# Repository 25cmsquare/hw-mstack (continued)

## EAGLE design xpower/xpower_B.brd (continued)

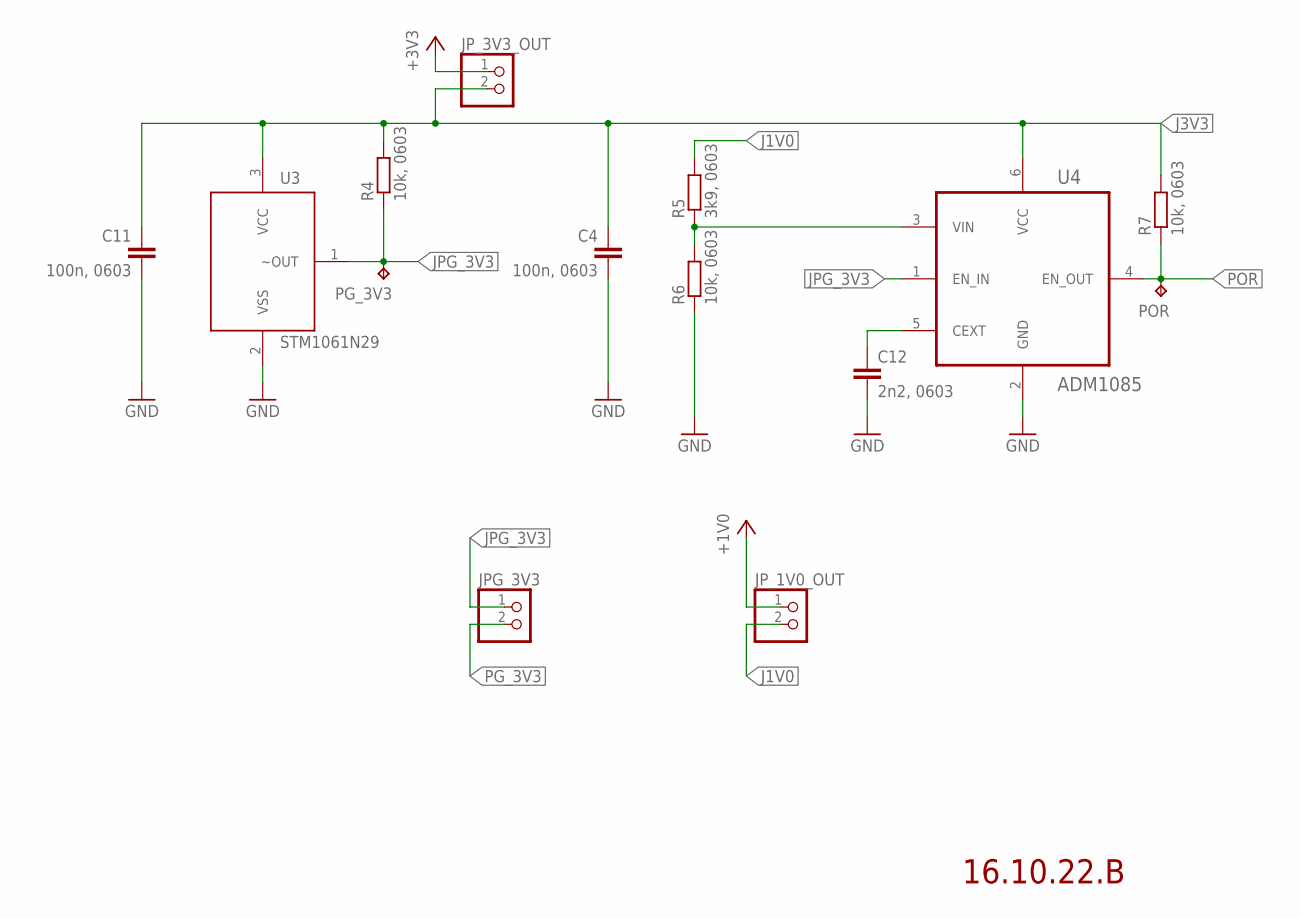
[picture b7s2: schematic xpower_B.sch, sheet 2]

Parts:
C4, C11: 100n, 0603; C0603
C12: 2n2, 0603; C0603
JPG_3V3: PINHD-1X2; 1X02
JP_1V0_OUT, JP_3V3_OUT: PINHD-1X2; 1X02
PG_3V3: TPTP14R; TP14R
POR: TPTP14R; TP14R
R4, R6, R7: 10k, 0603; R0603
R5: 3k9, 0603; R0603
U3: STM1061N29; SOT-23-3
U4: ADM1085; SOT65P210X110-6N

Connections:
+1V0: JP_1V0_OUT.1; also elsewhere on the board
+3V3: JP_3V3_OUT.1; also elsewhere on the board
CEXT: C12.1, U4.5 (CEXT)
GND: C4.2, C11.2, C12.2, R6.1, U3.2 (VSS), U4.2 (GND); also elsewhere on the board
J1V0: JP_1V0_OUT.2, R5.2
J3V3: C4.1, C11.1, JP_3V3_OUT.2, R4.2, R7.2, U3.3 (VCC), U4.6 (VCC)
JPG_3V3: JPG_3V3.1, PG_3V3.TP, R4.1, U3.1 (~OUT), U4.1 (EN_IN)
PG_3V3: JPG_3V3.2; also elsewhere on the board
POR: POR.TP, R7.1, U4.4 (EN_OUT); also elsewhere on the board
VIN: R5.1, R6.2, U4.3 (VIN)

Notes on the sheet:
16.10.22.B

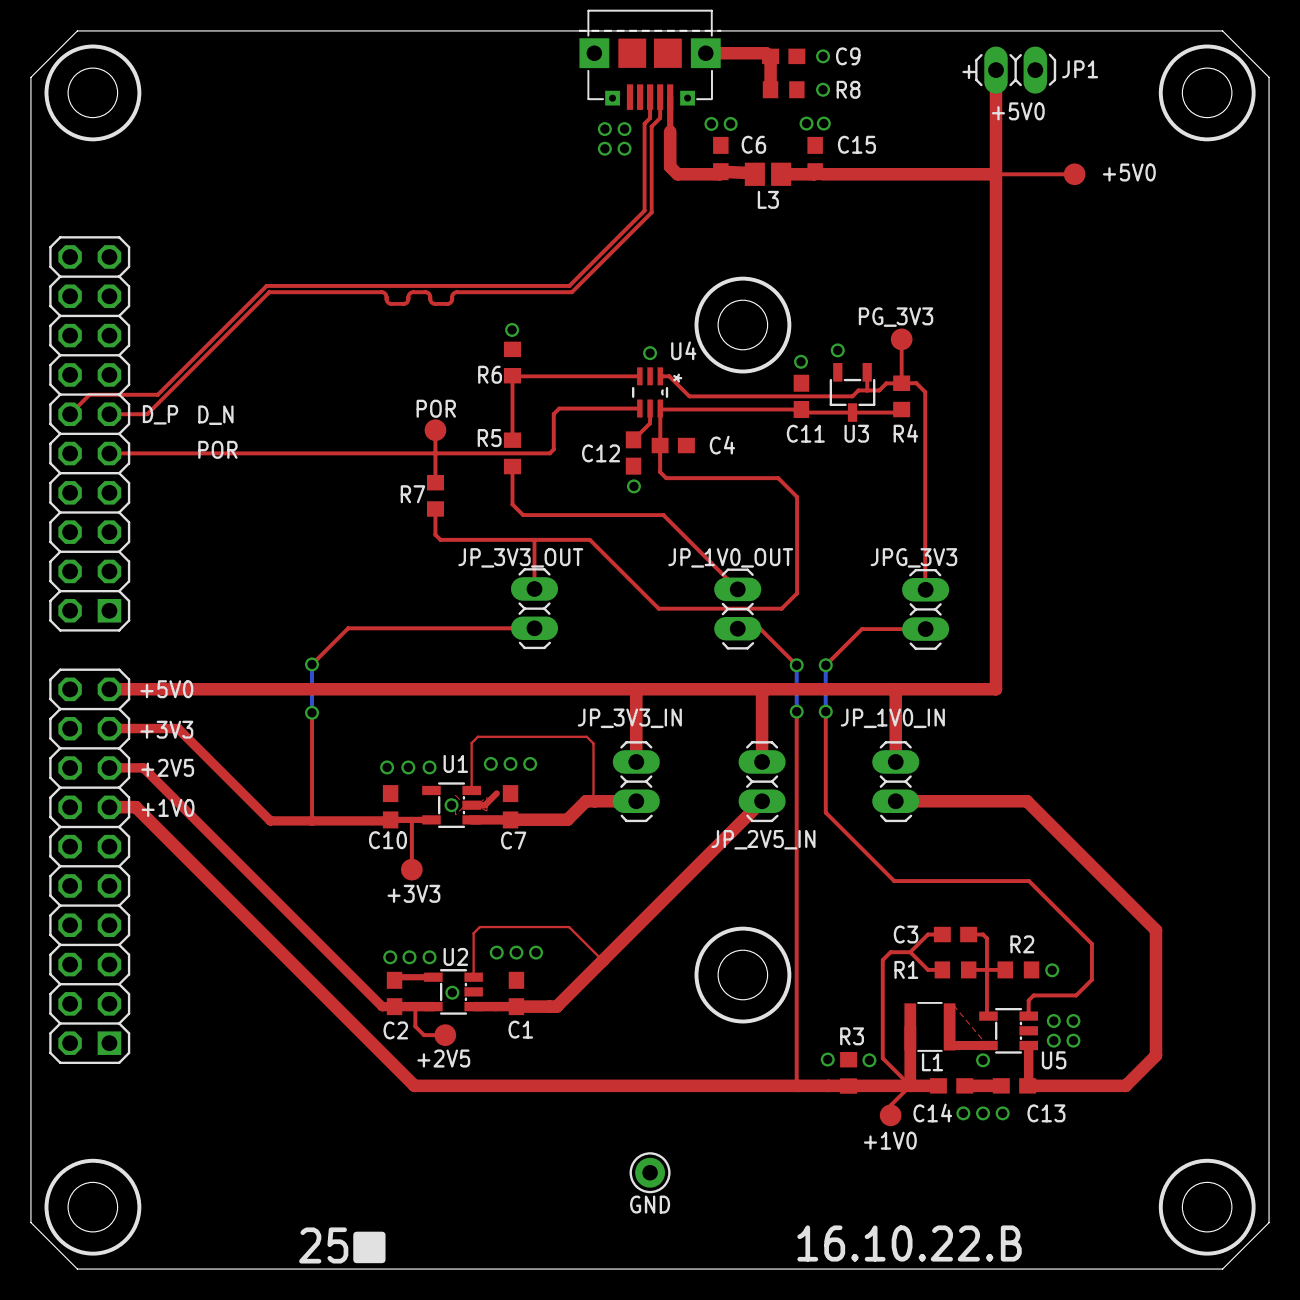
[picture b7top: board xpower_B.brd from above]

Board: 2 copper layers, 80.0 x 80.0 mm, 44 parts (1 on the bottom side), 21 nets.

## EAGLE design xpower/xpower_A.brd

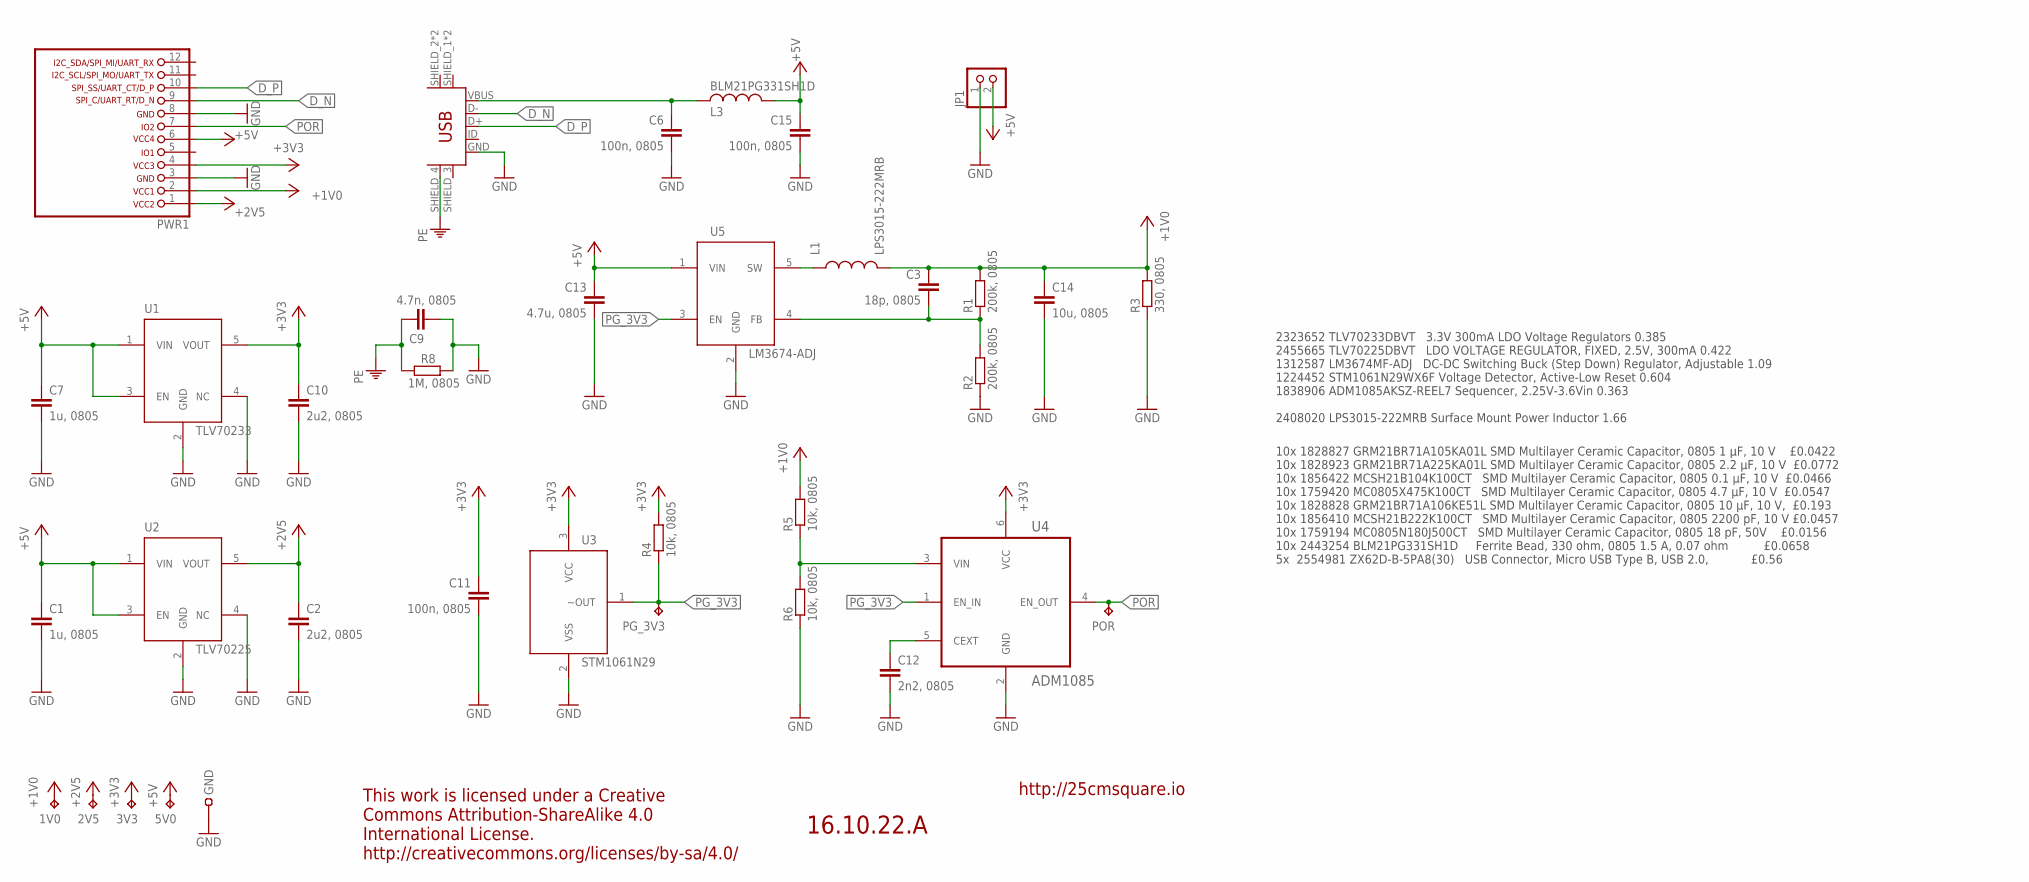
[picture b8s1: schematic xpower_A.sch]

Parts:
1V0, 2V5, 3V3, 5V0: TPTP14R; TP14R
C1, C7: 1u, 0805; C0805
C2, C10: 2u2, 0805; C0805
C3: 18p, 0805; C0805
C6, C11, C15: 100n, 0805; C0805
C9: 4.7n, 0805; C0805
C12: 2n2, 0805; C0805
C13: 4.7u, 0805; C0805
C14: 10u, 0805; C0805
GND: TEST-22-MULTICOMP; TEST_1MM
JP1: PINHD-1X2; 1X02
L1: LPS3015-222MRB; LPS3015
L3: BLM21PG331SH1D; R0805
PG_3V3: TPTP14R; TP14R
POR: TPTP14R; TP14R
PWR1: LIWE_12_PIN_PWR5X5; LIWE_12_PIN
R1, R2: 200k, 0805; R0805
R3: 330, 0805; R0805
R4, R5, R6: 10k, 0805; R0805
R8: 1M, 0805; R0805
U1: TLV70233; SOT-23-5
U2: TLV70225; SOT-23-5
U3: STM1061N29; SOT-23-3
U4: ADM1085; SOT65P210X110-6N
U5: LM3674-ADJ; SOT-23-5
U$5: ZX62D-B-5PA8

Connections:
+1V0: 1V0.TP, C3.1, C14.1, L1.P2 (2), PWR1.2, R1.2, R3.2, R5.2
+2V5: 2V5.TP, C2.1, PWR1.1, U2.5 (VOUT)
+3V3: 3V3.TP, C10.1, C11.1, PWR1.4, R4.2, U1.5 (VOUT), U3.3 (VCC), U4.6 (VCC)
+5V: 5V0.TP, C1.1, C7.1, C13.1, C15.1, JP1.2, L3.1, PWR1.6, U1.1 (VIN), U1.3 (EN), U2.1 (VIN), U2.3 (EN), U5.1 (VIN)
CEXT: C12.1, U4.5 (CEXT)
D_N: PWR1.9, U$5.D-
D_P: PWR1.10, U$5.D+
FB: C3.2, R1.1, R2.2, U5.4 (FB)
GND: C1.2, C2.2, C6.2, C7.2, C9.2, C10.2, C11.2, C12.2, C13.2, C14.2, C15.2, GND.1, JP1.1, PWR1.3, PWR1.8, R2.1, R3.1, R6.1, R8.1, U1.2 (GND), U1.4 (NC), U2.2 (GND), U2.4 (NC), U3.2 (VSS), U4.2 (GND), U5.2 (GND), U$5.GND
L: L1.P1 (1), U5.5 (SW)
PE: C9.1, R8.2, U$5.SHIELD_4 (MTN4)
PG_3V3: PG_3V3.TP, R4.1, U3.1 (~OUT), U4.1 (EN_IN), U5.3 (EN)
POR: POR.TP, PWR1.7, U4.4 (EN_OUT)
VBUS: C6.1, L3.2, U$5.VBUS
VIN: R5.1, R6.2, U4.3 (VIN)

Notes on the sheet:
16.10.22.A
This work is licensed under a Creative Commons Attribution-ShareAlike 4.0 International License. http://creativecommons.org/licenses/by-sa/4.0/
http://25cmsquare.io
2323652 TLV70233DBVT 3.3V 300mA LDO Voltage Regulators 0.385 2455665 TLV70225DBVT LDO VOLTAGE REGULATOR, FIXED, 2.5V, 300mA 0.422 1312587 LM3674MF-ADJ DC-DC Switching Buck (Step Down) Regulator, Adjustable 1.09 1224452 STM1061N29WX6F Voltage Detector, Active-Low Reset 0.604 1838906 ADM1085AKSZ-REEL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
10x 1828827 GRM21BR71A105KA01L SMD Multilayer Ceramic Capacitor, 0805 1 µF, 10 V £0.0422 10x 1828923 GRM21BR71A225KA01L SMD Multilayer Ceramic Capacitor, 0805 2.2 µF, 10 V £0.0772 10x 1856422 MCSH21B104K100CT SMD Multilayer Ceramic Capacitor, 0805 0.1 µF, 10 V £0.0466 10x 1759420 MC0805X475K100CT S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

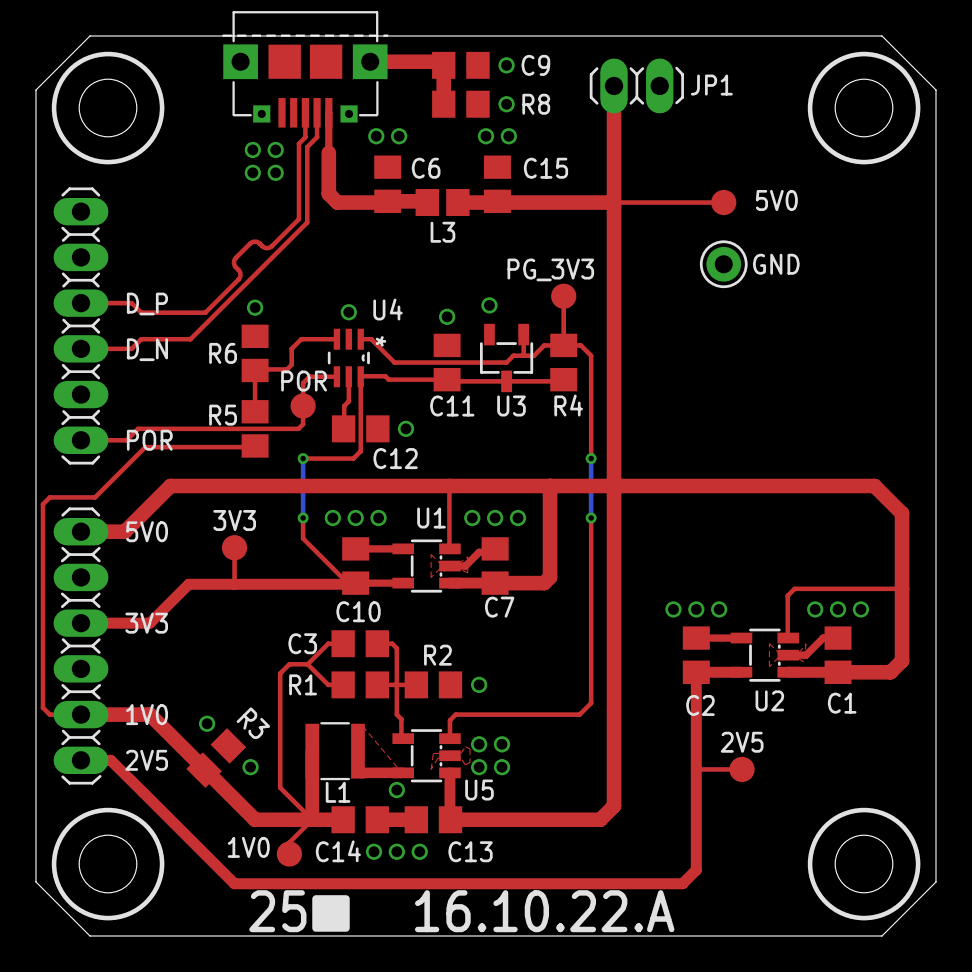
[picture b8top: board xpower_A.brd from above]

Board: 2 copper layers, 50.0 x 50.0 mm, 36 parts (1 on the bottom side), 15 nets.

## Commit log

2016-03-12 repo init
2016-03-12 Added psoc1 CY8C20246A board for adc test.
2016-03-12 Added LT3042 files.
2016-03-12 Added LM7705 files.
2016-03-13 Added TPS62730 files.
2016-03-13 TPS62730: added Application Note AN097 from TI
2016-04-24 Added lbr dir and 25cmsquare.lbr & pinhead.lbr files.
2016-04-24 Initial version of AT86RF233 for RPI 2 board
2016-04-25 lbr: KSR2XYG switch tweaking.
2016-04-25 at86rf233: added reset switch
2016-04-25 lbr: ATZB-RF-233-1-C package twekaing
2016-04-25 at86rf233: board created
2016-04-26 lbr: ATZB-RF-233-1-C: added resticted area for antenas
2016-04-26 at86rf233: updated with recent package
2016-04-27 lbr: KSR2XYG switch added >NAME >VALUE
2016-04-27 at86rf233: SW1 renamed to RESET & minor alignemt improvements.
2016-04-28 at86rf233: board finalizing
2016-04-28 at86rf233: Generated gerber files
2016-04-29 at86rf233: Generated pdf schematic
2016-05-04 lbr: added SI7021, BME1080 and HDC1080
2016-05-04 temp_array: initial schema
2016-05-05 lbr: added SHT11 device
2016-05-09 temp_array: added PCA9548APWR
2016-05-17 temp_array: pcb routing
2016-05-18 lbr: added BGM111 device
2016-06-01 Added BGB111 schema/board
2016-06-01 lbr: added OSHW logo device
2016-06-01 bgm111: added gerbers
2016-06-06 temp array: added PCB pictures
2016-06-06 at86rf233: added PCB pictures
2016-06-06 bgm111: added schema pdf
2016-09-20 Added 5P49V5923 Programmable Clock Generator
2016-10-20 Added sot-23-5, TLV702 and +2V5.
2016-10-20 WIP: xpower 1V0, 2V5, 3V3 and 5V0 suply with POR output.
2016-10-22 Added sot-23-2 package and stm1061 symbol & device
2016-10-22 Added ADM1085 device
2016-10-22 Added 1V0 symbol/device
2016-10-22 Added LM3674-ADJ device.
2016-10-22 lbr: LIWE_12_PIN_PWR more general pin names.
2016-10-22 lbr: fixed ADM1085 symbol
2016-10-22 WIP: xpower - added 1V0
2016-10-23 lbr: LIWE_12_PIN_PWRL added D_P and D_N
2016-10-23 WIP: xpower - added USB
2016-10-24 lbr: added TXC 9C and ECX 53B xtals.
2016-10-27 WIP: xpower - minor final tweaks.
2016-10-29 WIP: xpower - PCB
2016-10-30 lib: minor silk screen fixes
2016-10-30 xpower: finished PCB.
2016-11-02 lbr: minor beautifications
2016-11-02 xclock: WIP first draft.
2016-11-03 lbr: added pinhead 3x7/90
2016-11-03 xclock: use pinhead 3x7 and added temp sensor.
2016-11-05 lib: si7021 increased pads size for easy hand soldering
2016-11-05 xclock: finished + PCB
2016-11-06 lbr: added XEF216-512-TQ128
2016-11-08 lbr: pinhead renamed to 25pinhead
2016-11-08 lbr: XEF216-512-TQ128 tweaking
2016-11-08 lbr: added X13/90 into the pinhead
2016-11-08 xclock: new pinhead 3x7 symbol
2016-11-09 lbr: 25pinhead tweaking
2016-11-09 lbr: added NC7WZ07
2016-11-09 xcore: WIP initial schema draft
2016-11-10 xcore: WIP schema
2016-11-14 xcore: WIP jtag chaining.
2016-11-16 xcore: WIP power & decoupling
2016-11-17 lbr: added LIWE_12_PIN_7X7_COMPAT package
2016-11-17 lbr: added PINHD-3X21 device
2016-11-17 xcore: updated with LIWE 7x7 and 3x21 pin header
2016-11-17 xcore: WIP brd first draft
2016-11-21 lbr: added NC7WZ240 device in SOP50P310X90-8N package.
2016-11-21 lbr: added FIN1002 device and SOP50P310X90-8N package.
2016-11-21 lbr: added NC7SZ175 device
2016-11-21 spdif: WIP initial schema.
2016-11-22 lbr: added PLR135_T10 device
2016-11-22 lbr: added RCJ-01X
2016-11-22 lbr: added PESD0603-240 device with ZD symbol
2016-11-22 lbr: added DM103MC device
2016-11-22 lbr: added PLT133_T10W device
2016-11-22 lbr: added FIN1001 device
2016-11-22 lbr: srhinking NC7SZ175 symbol
2016-11-22 lbr: DM103MC renamed/fixed to DA101MC.
2016-11-22 lbr: added proper FB device
2016-11-22 spdif: WIP schematic
2016-11-22 lbr: da101mc package tweaking
2016-11-22 spdif: WIP pcb
2016-11-23 lbr: fixed PLT133_T10W pinout
2016-11-23 lbr: fixed RCJ-01X drc warning.
2016-11-23 lbr: minor tweak in 25pinhead 2x6
2016-11-23 lbr: minor silkscreen fixes
2016-11-23 spdif: finished PCB
2016-11-23 added gitignore file
2016-11-23 spdif: minor pcb beautification.
2016-11-23 spdif: added conns datasheets
2016-11-23 spdif: added gerber files
2016-11-23 xpower: BOM farnell lookup
2016-11-23 xclock: added gerber files
2016-11-23 xpower: added doc files
2016-11-23 spdif: fixed JP2 position - regenerated gerbers.
2016-11-27 xcore: part number for pinhead 3x21
2016-12-02 lbr: fixed silkscreen on SOT65P210X110-6N package.
2016-12-02 xpower: minor beautifications
2016-12-02 lbr: added LIWE_12_PIN_10X10_COMPAT package.
2016-12-02 lbr: added LIWE_12_PIN_8X8_COMPAT package.
2016-12-02 xcore: updated PWR to LIWE_12_PIN_8X8_COMPAT
2016-12-02 lbr: added PINHD-3X25 device
2016-12-05 spdif: added partlist for digikey
2016-12-06 xpower: WIP version B
2016-12-06 xpower: A version measurements.
2016-12-08 xcore: WIP PCB
2016-12-10 lbr: fixed silkscreen warning
2016-12-12 lbr: fixed route="any" on xmos VDDIOR
2016-12-12 lbr: fixed RCJ-01X package.
2016-12-12 spdif: WIP B version with 80x80 base
2016-12-12 lbr: added 8 more pins on liwe 12 pin 8x8
2016-12-12 spdif: updated new liwe conn + minor tweaks.
2016-12-13 lbr: introduced liwe 40 8x8 device.
2016-12-13 xcore: updated with liwe 40 8x8 device
2016-12-14 lbr: fixed liwe 40 IO pins ordering
2016-12-15 lbr: added two more clock signals on liwe 40 io header.
2016-12-30 lbr: pinhead added 3X25/90/M
2016-12-31 lbr: fixed 3X25/90 origin
2016-12-31 xcore: PCB finished
2016-12-31 xcore: PCB final tweaks
2017-01-01 xclock: WIP B variant
2017-01-01 lbr: update 3x cons symbol names to fit the lib
2017-01-01 xcore: updated with new 3x con symbol names
2017-01-01 lbr: pinhead added 3X08/90 pinhead
2017-01-02 xcore: added gerber files
2017-01-03 xclock: B variant finished PCB
2017-01-03 xpower: B variant PCB finished
2017-01-03 xpower: added gerber files
2017-01-03 xpower: minor update
2017-01-03 spdif: B variant PCB finished
2017-01-06 spdif: added diff signaling for TX/RX 2
2017-01-06 xcore: added differential I/O for x0d38 and x0d39 (spdif I/O)
2017-01-07 xpower: final tweaks
2017-01-07 xclock: final tweaks
2017-01-07 spdif: final tweaks
2017-01-07 xcore: final tweaks
2017-02-13 xcore: added BOM_A
2017-02-13 lbr: added cs4384 and sta311b
2017-02-13 xout: WIP first schematic draft.
2017-02-14 xaout renamed to xdac
2017-02-14 lbr: added philips elyt caps + minor tweaks for sta311b & cs4384
2017-02-14 xdac: VIP schematic in progress.
2017-02-14 lbr: sta311b tweaking
2017-02-21 lib: 25pinhead - added 3x9, 3x5 + minor tweaks of 3x8
2017-02-22 lbr: added NAME & VALUE for IDT symbol
2017-02-22 xclock: update with recent library changes + xtal cap values updated to 15p
2017-02-28 lbr: added name to 3.5mm jack package.
2017-02-28 xdac: PCB WIP
2017-03-22 lbr: added elyt cap EEE-FC1C220R
2017-03-22 xdac: VIP
2017-03-24 xdac: WIP
2017-03-27 lbr: minor silk screen fixes
2017-03-28 xdac: finished PCB
2017-03-28 lbr: minor tweaks
2017-03-28 xdac: update with recent lib changes
2017-03-28 Added modulator sta311b - xmod chema & board - VIP
2017-03-29 xmod: PCB finished
2017-03-29 xdac: added gerber files and pdf.
2017-03-29 xmod: added gerber files and pdf.
2017-05-05 xmod: fixed capacitor type in output filter
2017-05-10 xdac: added BOM
2017-05-10 lbr: added CS42526 in LQFP 64
2017-05-10 xcodec: WIP
2017-05-11 lbr: minor silkscreen layer tweaking.
2017-05-16 lbr: minor silkscreen tweaking.
2017-05-16 xcodec: finished PCB.
2017-05-17 xcodec: final DSP
2017-12-04 added xdac+xpower.
2017-12-04 xcodec: manual merge from upstream.
2017-12-04 xdac+power: added pdf schematics.
2017-12-04 xdac+power: renamed files to proper names.
2017-12-04 xdac+power: minor schematics pdf update.
